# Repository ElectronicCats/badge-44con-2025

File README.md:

# Hardware config 

Attention! Reading this README is essential—not only for a better understanding and experience, but also to avoid damaging the badge.

The 44con can operate either with the ESP32 or with the shield. It is important to note that, for the badge to function correctly, at least one of the two must be soldered. Otherwise, the badge will not work.

When the shield is installed, the badge will only operate the OLED display with the built-in mini-game.

(Badge with shield)

# 
If you solder the shield you only need to solder the bended pins shown at the photo at least, if you decide to solder more pins just for fun go ahead.

#
For the best possible experience with the badge, it is recommended to solder the ESP32 with the following components:

ESP32 Wemos D1 module

Buzzer

MT3608 Boost Converter

AD8317 RF Detector

# Addon 

The Addon is located on the front side of the board, and the connections are as follows:

# Boost circuit
It raises the voltage from 5 V to 9 V for the RF detector. The Boost circuit must be placed on the rear side of the board, as shown in the image. 

<br>

# I²C jumper 
The I²C jumpers are located on the rear side of the board (JP3 for SCL and JP2 for SDA). These determine whether the ESP32 or the CH32 will control the OLED display. By default, the CH32 controls the display. To switch control to the ESP32, the pads must be cut to separate them (as indicated in the image), and then the central pad must be soldered to the opposite pad. In the case of JP2, solder the central pad to the left pad, and for JP3, solder it to the right pad.

# Potenciometer
The potentiometer must be installed on the rear side of the board, ensuring that its notch fits into the corresponding slot, allowing the value to be adjusted from the front side of the PCB. 

This is how it should look, front and back.

# Buzzer
For the buzzer, please solder it as follows:

# RF Detector 
It detects hidden wireless devices by measuring RF signal strength and displaying results on an OLED screen, with optional buzzer alerts.

The RF detector must be placed on the rear side of the PCB, as shown in the image. IMPORTANT: Before soldering the RF module, first solder the Boost circuit and configure its voltage to 9 V to ensure proper operation of the RF detector and prevent damage. The PCB has the supply voltage (9VA) disconnected via JP1 to avoid damage. Only bridge it after confirming that the voltage is correct.
For more information about the functionality, please refer to the following repository: https://github.com/RamboRogers/rfhunter

<br>

This project uses and builds upon the work of rfhunter by RamboRogers.

The original firmware and repository can be found here: https://github.com/RamboRogers/rfhunter

We acknowledge and thank the original author for making this project available!

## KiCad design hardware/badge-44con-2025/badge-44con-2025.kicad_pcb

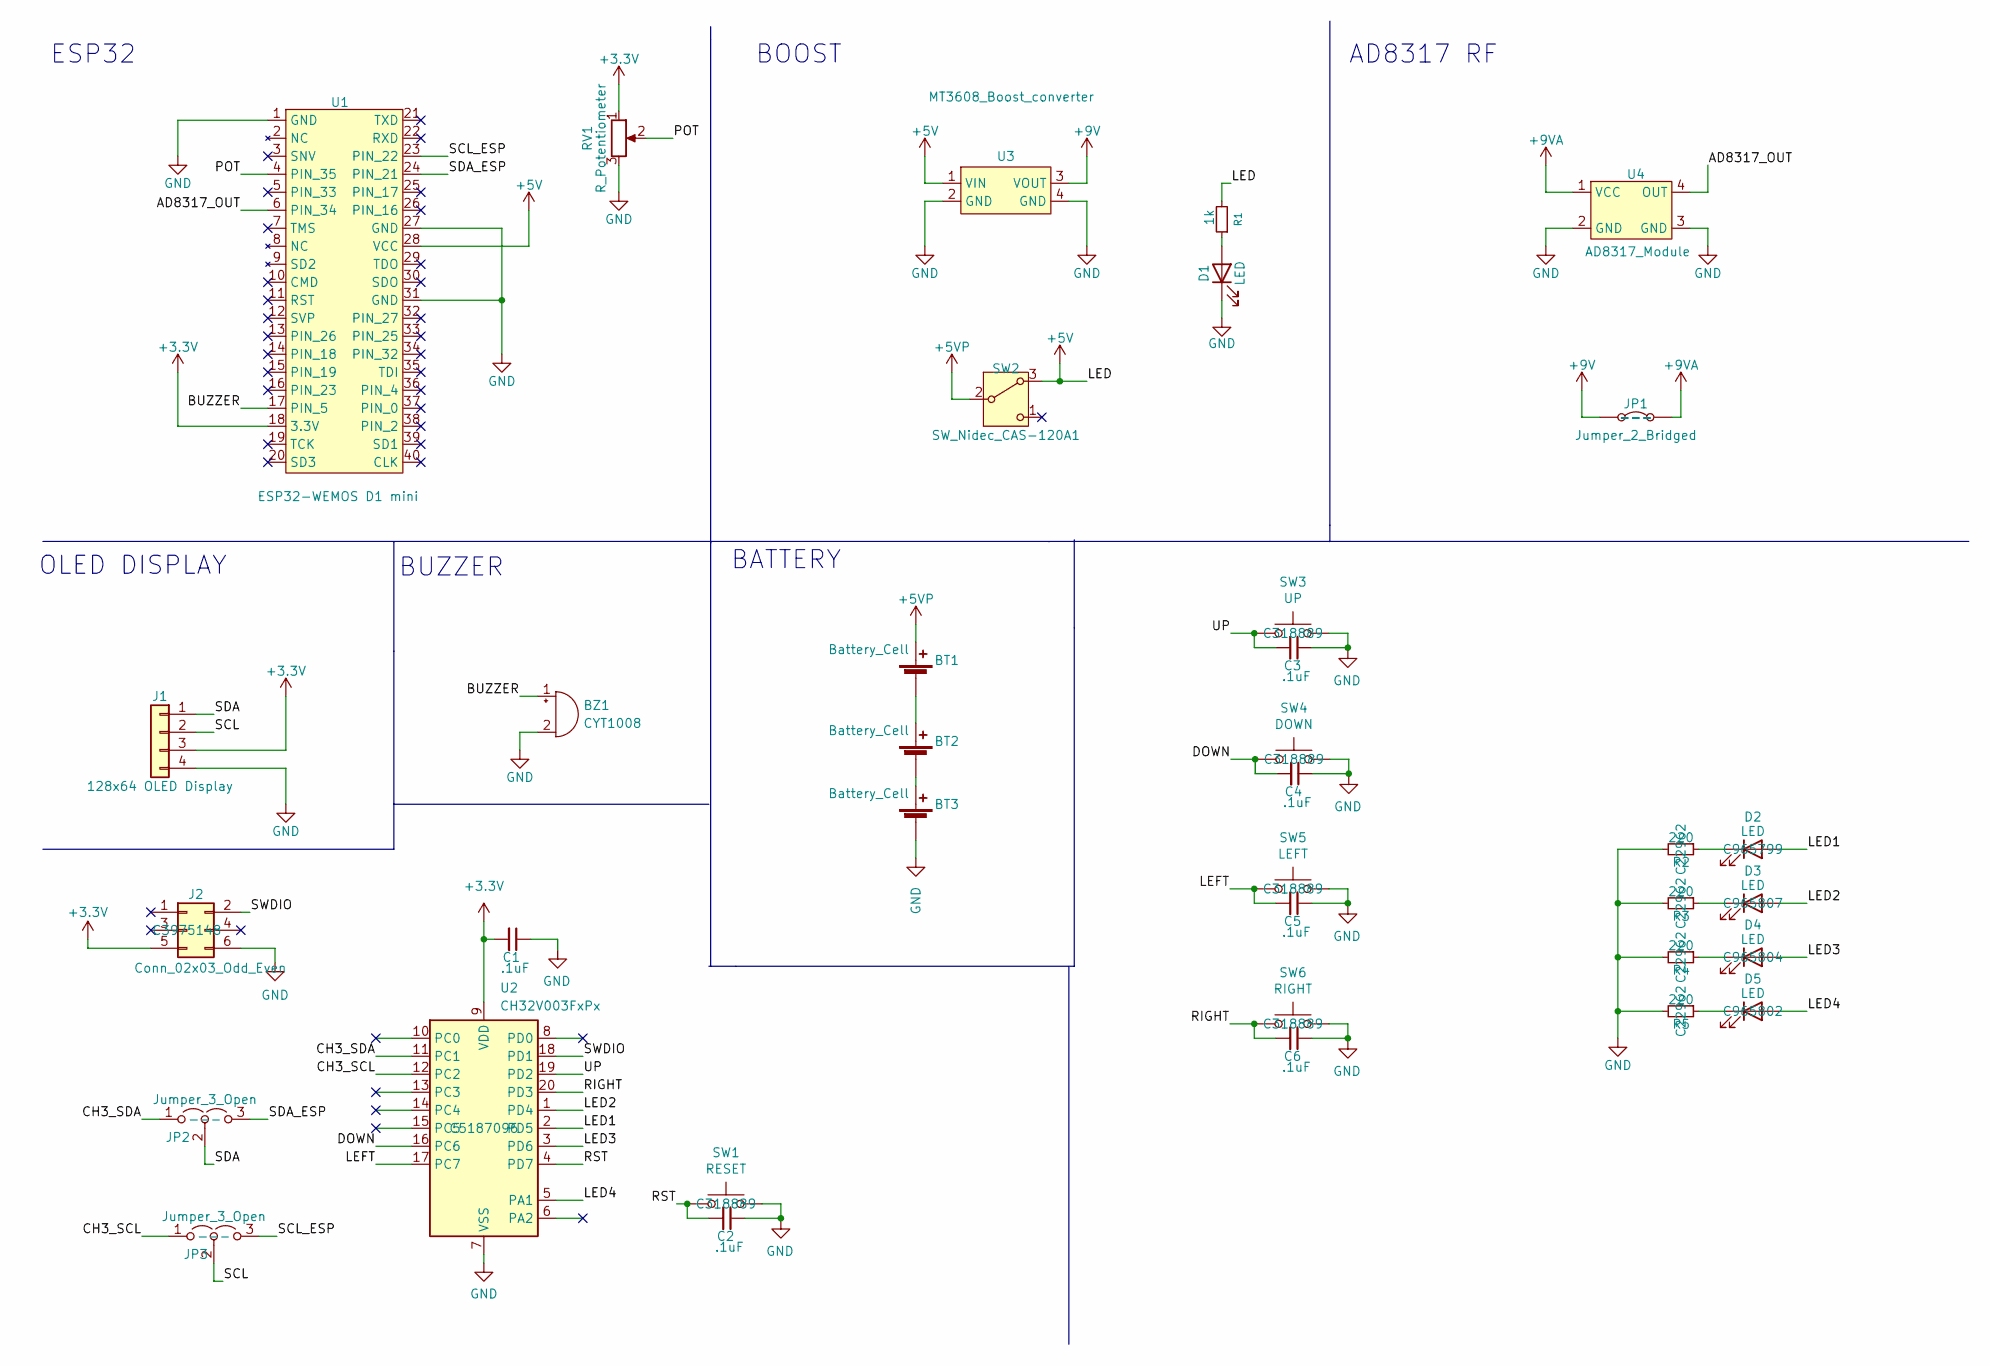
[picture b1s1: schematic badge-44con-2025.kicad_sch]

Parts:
BT1, BT2, BT3: Battery_Cell; BatteryHolder_Keystone_2466_1xAAA; LCSC# C5290189
BZ1: CYT1008; Buzzer_12x9.5RM7.6
C1, C2, C3, C4, C5, C6: .1uF; C_0603_1608Metric; LCSC# C478888
D1: LED; LED_0603_1608Metric
D2: LED; LED_0603_1608Metric; LCSC# C965799
D3: LED; LED_0603_1608Metric; LCSC# C965807
D4: LED; LED_0603_1608Metric; LCSC# C965804
D5: LED; LED_0603_1608Metric; LCSC# C965802
J1: 128x64 OLED Display; MODULE_DM-OLED096-636
J2: Conn_02x03_Odd_Even; PinHeader_2x03_P2.54mm_Vertical_SMD; LCSC# C3975148
JP1: Jumper_2_Bridged; PinHeader_1x02_P2.54mm_Vertical
JP2, JP3: Jumper_3_Open; SolderJumper-3_P1.3mm_Bridged2Bar12_RoundedPad1.0x1.5mm
R1: 1k; R_0603_1608Metric
R2, R3, R4, R5: 220; R_0603_1608Metric; LCSC# C22962
RV1: R_Potentiometer; Potentiometer_generic
SW1: RESET; SW_SPST_TL3342; LCSC# C318889
SW2: SW_Nidec_CAS-120A1; JS102011SAQN
SW3: UP; SW_SPST_TL3342; LCSC# C318889
SW4: DOWN; SW_SPST_TL3342; LCSC# C318889
SW5: LEFT; SW_SPST_TL3342; LCSC# C318889
SW6: RIGHT; SW_SPST_TL3342; LCSC# C318889
U1: ESP32-WEMOS D1 mini; Wemos Mini D1 ESP WiFi + Bluetooth CP2104
U2: CH32V003FxPx; TSSOP-20_4.4x6.5mm_P0.65mm; LCSC# C5187096
U3: MT3608_Boost_converter; MT3608
U4: AD8317_Module; AD8317

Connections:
+3.3V: C1.2, J1.3, J2.5, RV1.1, U1.18 (3.3V), U2.9 (VDD)
+5V: R1.2, SW2.3 (A), U1.28 (VCC), U3.1 (VIN)
+5VP: BT1.1 (+), SW2.2 (B)
+9V: JP1.1 (A), U3.3 (VOUT)
+9VA: JP1.2 (B), U4.1 (VCC)
/AD8317_OUT: U1.6 (PIN_34), U4.4 (OUT)
/BUZZER: BZ1.1 (+), U1.17 (PIN_5)
/CH3_SCL: JP3.1 (A), U2.12 (PC2)
/CH3_SDA: JP2.1 (A), U2.11 (PC1)
/DOWN: C4.2, SW4.2, U2.16 (PC6)
/LED1: D2.2 (A), U2.2 (PD5)
/LED2: D3.2 (A), U2.1 (PD4)
/LED3: D4.2 (A), U2.3 (PD6)
/LED4: D5.2 (A), U2.5 (PA1)
/LEFT: C5.2, SW5.2, U2.17 (PC7)
/POT: RV1.2, U1.4 (PIN_35)
/RIGHT: C6.2, SW6.2, U2.20 (PD3)
/RST: C2.2, SW1.2, U2.4 (PD7)
/SCL: J1.2, JP3.2 (C)
/SCL_ESP: JP3.3 (B), U1.23 (PIN_22)
/SDA: J1.1, JP2.2 (C)
/SDA_ESP: JP2.3 (B), U1.24 (PIN_21)
/SWDIO: J2.2, U2.18 (PD1)
/UP: C3.2, SW3.2, U2.19 (PD2)
GND: BT3.2 (-), BZ1.2 (-), C1.1, C2.1, C3.1, C4.1, C5.1, C6.1, D1.1 (K), J1.4, J2.6, R2.2, R3.2, R4.2, R5.2, RV1.3, SW1.1, SW3.1, SW4.1, SW5.1, SW6.1, U1.1 (GND), U1.27 (GND), U1.31 (GND), U2.7 (VSS), U3.2 (GND), U3.4 (GND), U4.2 (GND), U4.3 (GND)
unnamed: BT1.2 (-), BT2.1 (+)
unnamed: BT2.2 (-), BT3.1 (+)
unnamed: D1.2 (A), R1.1
unnamed: D2.1 (K), R2.1
unnamed: D3.1 (K), R3.1
unnamed: D4.1 (K), R4.1
unnamed: D5.1 (K), R5.1

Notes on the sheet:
AD8317 RF
BATTERY
ESP32
BUZZER
BOOST
OLED DISPLAY

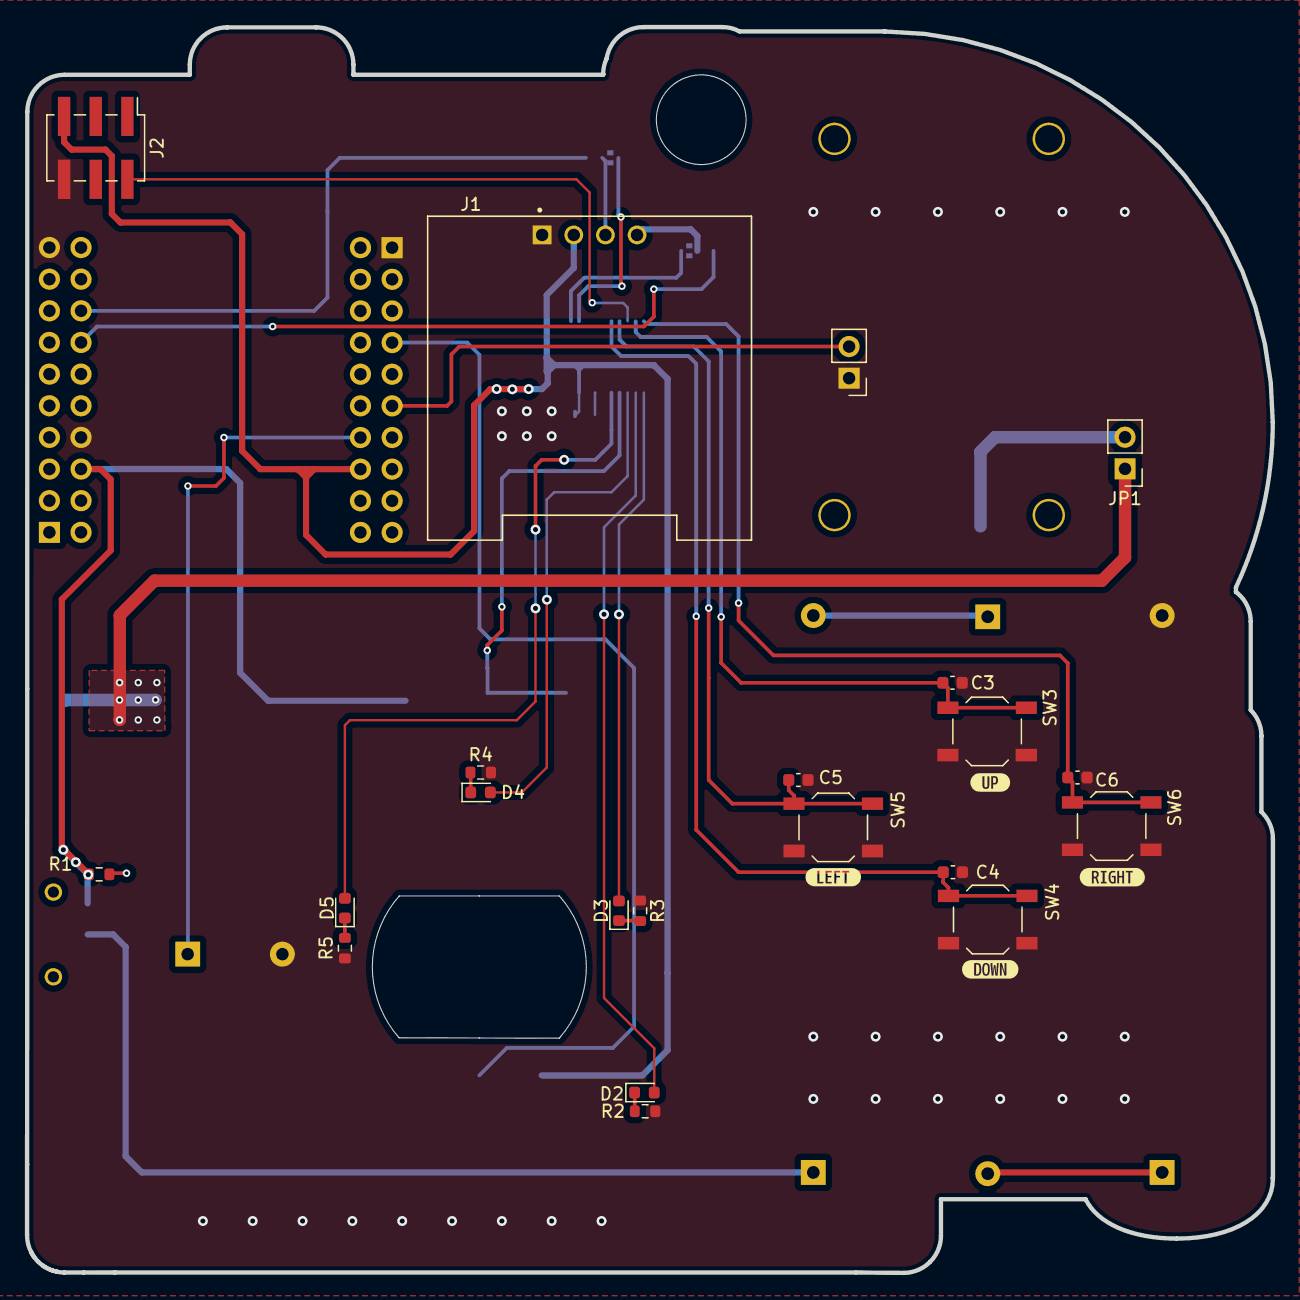
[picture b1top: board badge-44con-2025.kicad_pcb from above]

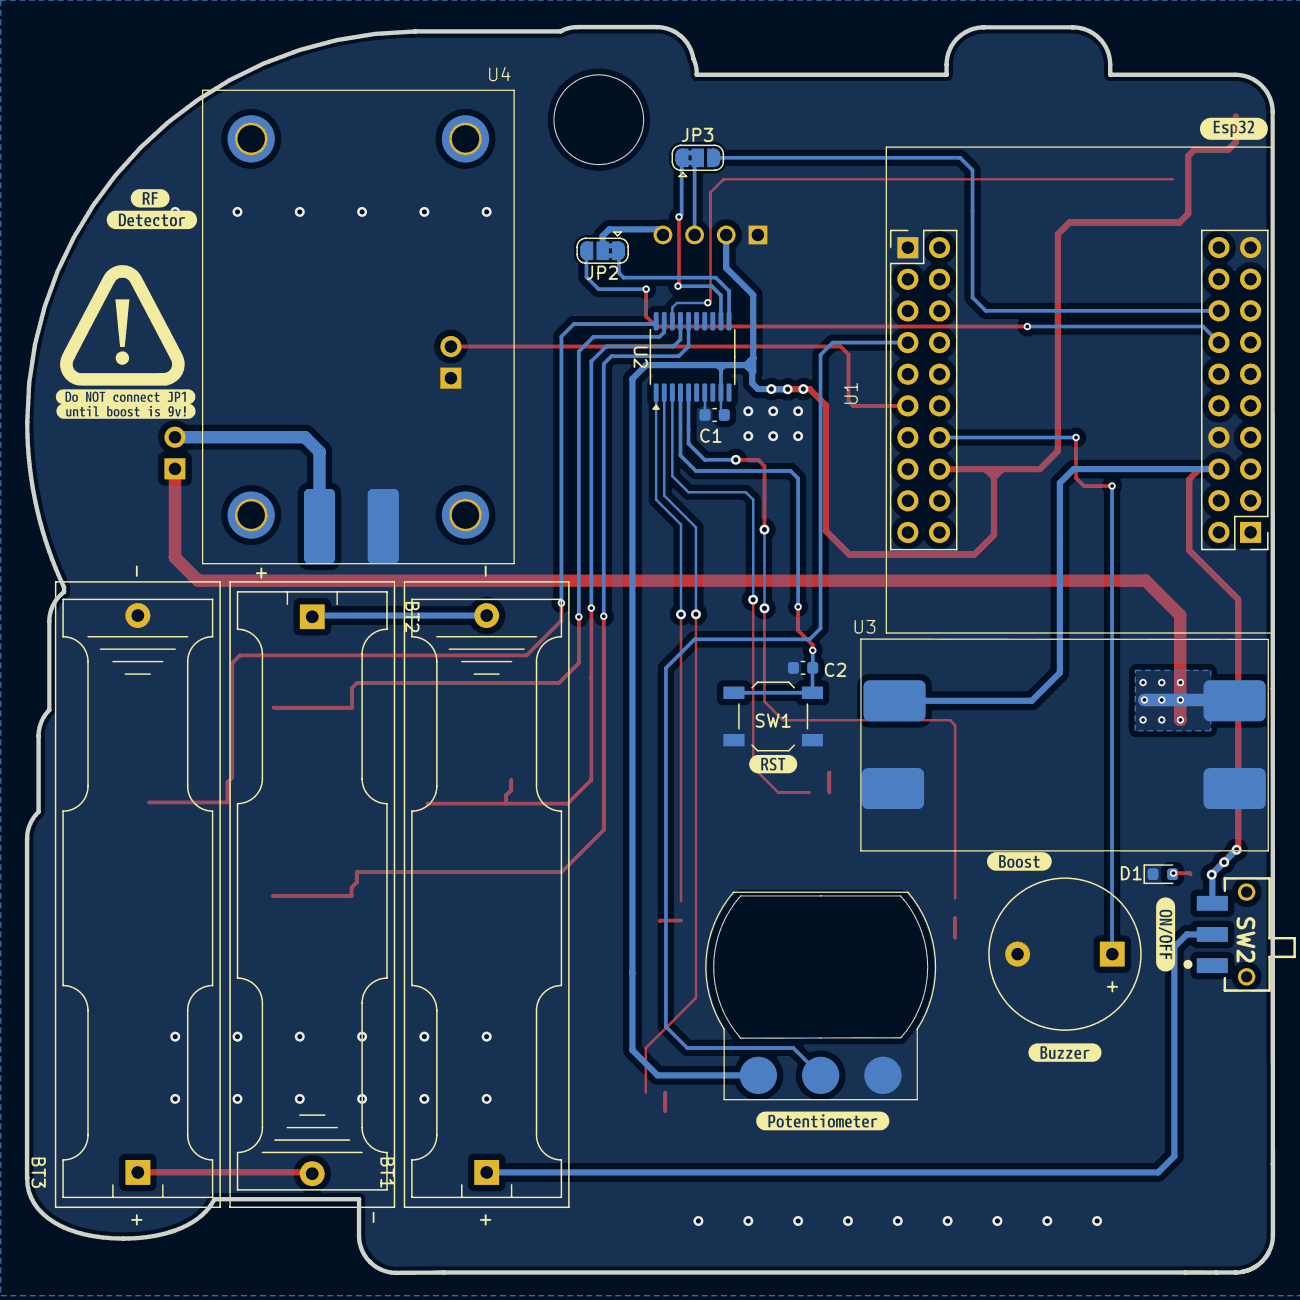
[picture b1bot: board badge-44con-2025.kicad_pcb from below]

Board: 2 copper layers, 100.0 x 100.0 mm, 50 parts (25 on the bottom side), 32 nets.

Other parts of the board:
kibuzzard-68957B6E: G***; kibuzzard-68957B6E
kibuzzard-68957F6B: G***; kibuzzard-68957F6B
kibuzzard-689576B7: G***; kibuzzard-689576B7
kibuzzard-689576CB: G***; kibuzzard-689576CB
kibuzzard-689576F4: G***; kibuzzard-689576F4
kibuzzard-689576FF: G***; kibuzzard-689576FF
kibuzzard-689581B6: G***; kibuzzard-689581B6
kibuzzard-689585C0: G***; kibuzzard-689585C0
kibuzzard-689585CD: G***; kibuzzard-689585CD
kibuzzard-689585DD: G***; kibuzzard-689585DD
kibuzzard-689585EE: G***; kibuzzard-689585EE
kibuzzard-6895857B: G***; kibuzzard-6895857B
kibuzzard-68957673: G***; kibuzzard-68957673
kibuzzard-68958540: G***; kibuzzard-68958540

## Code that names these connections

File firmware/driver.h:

#pragma once

#include "ch32fun.h"
#include "oled_min.h"

/**
 * Driver for the game of the badge 44con here comes where it detects the buttons and oled
 * 
 * This functions are adapted for the games from this repository https://github.com/wagiminator/CH32V003-GameConsole
 */

// Buttons in the badge
#define BUTTON_UP       PD2
#define BUTTON_DOWN     PC6
#define BUTTON_LEFT     PC7 
#define BUTTON_RIGHT    PD3

// Leds in the badge
#define LED1    PD5
#define LED2    PD4
#define LED3    PD6
#define LED4    PA1

#define JOY_SOUND 0 // On 0 because there's no buzzer connected in the CH32 chip
#define BUZZER  PC3

#ifdef __cplusplus
extern "C" {
#endif

// Oled defines
#define JOY_OLED_init             OLED_init
#define JOY_OLED_end              I2C_stop
#define JOY_OLED_send(b)          I2C_write(b)
#define JOY_OLED_send_command(c)  OLED_send_command(c)
#define JOY_OLED_data_start(y)    {OLED_setpos(0,y);OLED_data_start();}

// Function to start the gpios and oled for the badge
void JOY_init(void){

    // Init the system
    SystemInit();

    // Init ports
    funGpioInitAll();

    // Set buttons config
    funPinMode(BUTTON_DOWN, GPIO_CNF_IN_PUPD);
    funPinMode(BUTTON_RIGHT, GPIO_CNF_IN_PUPD);
    funPinMode(BUTTON_LEFT, GPIO_CNF_IN_PUPD);
    funPinMode(BUTTON_UP, GPIO_CNF_IN_PUPD);

    // Init buttons
    funDigitalWrite(BUTTON_DOWN,1);
    funDigitalWrite(BUTTON_RIGHT,1);
    funDigitalWrite(BUTTON_LEFT,1);
    funDigitalWrite(BUTTON_UP,1);

    // Set leds config
    funPinMode(LED1, GPIO_Speed_10MHz | GPIO_CNF_OUT_PP);
    funPinMode(LED2, GPIO_Speed_10MHz | GPIO_CNF_OUT_PP);
    funPinMode(LED3, GPIO_Speed_10MHz | GPIO_CNF_OUT_PP);
    funPinMode(LED4, GPIO_Speed_10MHz | GPIO_CNF_OUT_PP);

    #if JOY_SOUND
    funPinMode(BUZZER, GPIO_Speed_10MHz | GPIO_CNF_OUT_PP);
    #endif

    // Init Oled
    OLED_init();
}

#define JOY_act_pressed() 1

uint8_t JOY_START(){
    return !funDigitalRead(BUTTON_UP) || !funDigitalRead(BUTTON_DOWN) || !funDigitalRead(BUTTON_LEFT) || !funDigitalRead(BUTTON_RIGHT); 
} 

uint8_t JOY_up_pressed(void){
    return funDigitalRead(BUTTON_UP);
}

uint8_t JOY_down_pressed(void){
    return funDigitalRead(BUTTON_DOWN);
}

uint8_t JOY_left_pressed(void){
    return funDigitalRead(BUTTON_LEFT);
}

uint8_t JOY_right_pressed(void){
    return funDigitalRead(BUTTON_RIGHT);
}


#define JOY_DLY_ms(n)   Delay_Ms(n)
#define JOY_DLY_us(n)   Delay_Us(n)

#define JOY_SLOWDOWN()    Delay_Ms(20)

// Pseudo random number generator
uint16_t rnval = 0xACE1;
uint16_t JOY_random(void) {
  rnval = (rnval >> 0x01) ^ (-(rnval & 0x01) & 0xB400);
  return rnval;
}

// Buzzer
void JOY_sound(uint8_t freq, uint8_t dur) {
    #if JOY_SOUND 
    while(dur--) {
        JOY_DLY_us(255 - freq);
        funDigitalWrite(BUZZER,1);
        JOY_DLY_us(255 - freq);
        funDigitalWrite(BUZZER,0);
    }
    #endif
}

#ifdef __cplusplus
};
#endif

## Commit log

2025-07-31 feat(Hw):Started_SCH
2025-08-01 feat(Hw): Finished_SCH
2025-08-05 Feat(Hw): Added_footprints
2025-08-06 feat(Hw): floorplan_draft
2025-08-06 feat(Hw):Added_microcontroller
2025-08-06 fix(Hw): Changed_PCB_design
2025-08-07 feat(Hw): Started routing
2025-08-08 feat(Hw): finished_routing
2025-08-08 fix(Hw):fixed_BOM
2025-08-08 fix(Hw):fixed_minor_pcb_details
2025-08-08 feat(Hw):Added_labels_and_changed_switch
2025-08-08 fix(Hw):Fixed_switch_in_BOM
2025-08-08 feat(Hw):Added_buttons
2025-08-08 fix(Hw): fixed_leds_BOM
2025-08-08 feat(Hw):Footprints_replaced
2025-09-04 feat: add game firmware
2025-09-04 Feat(Hw): Updated_BOM
2025-09-04 feat: add spaces for the logo
2025-09-05 fix: delete submodule
2025-09-05 feat: add ch32fun
2025-09-05 feat: add led sequence for waiting
2025-09-05 feat(fw): add sequence when the pacman dies
2025-09-05 feat: add led sequences for the game
2025-09-05 refactor(fw): include sequences in functions
2025-09-05 feat(hw): add logo for the begining
2025-09-05 Create Add-on
2025-09-05 Added_images_for_README
2025-09-12 Added_images_and_updated_readme
2025-09-18 Added_image_for_shield
2025-09-18 Create LICENSE
